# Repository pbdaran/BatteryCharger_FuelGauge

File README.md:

# Breakout Board: Battery Charger & Fuel Gauge — Design Story and Choices

Designing a compact, reliable battery management breakout board isn’t just about cramming chips together — it’s about understanding the trade-offs behind every component choice.  
Here’s the thinking behind the **Battery Charger & Fuel Gauge Breakout Board** and why I chose the ICs I did.

## 1. The Battery Charger: BQ24040 vs. TP4056

The **TP4056** has earned its fame in the maker world — it’s cheap, easy to use, and well supported. But it hides a quirk that can cause headaches in certain designs.

**The TP4056 quirk:**
- Pre-charge threshold: ~3.0 V
- Fixed pre-charge (trickle charge) current: **10 mA**
- If your battery is below 3 V and you have an **LDO** pulling ~10 mA from the charger output (to power 3.3 V logic, for instance), the TP4056 will happily supply that current to the LDO… **and zero to the battery**.
- Result? The battery never rises above 3 V, and the charger never switches to constant current mode. Stalemate.

**How the BQ24040 solves it:**
- **Lower pre-charge threshold**: ~2.5 V (battery starts charging earlier in its discharge)
- **Configurable pre-charge current**: e.g., 50 mA — plenty to both feed your LDO and still trickle energy into the cell.
- Additional perks:
  - Power path management: can supply load and charge battery simultaneously.
  - Status outputs for charge and fault indication.
  - Thermal regulation built in.

This means your system boots faster from a dead battery, and you don’t get stuck in a “never charging” deadlock.

## 2. The Fuel Gauge: BQ27621-G1 and the Calibration Dilemma

Battery fuel gauging is trickier than it looks. You can measure voltage, but it doesn’t tell the whole story about state of charge (SoC).

**Two main approaches:**
1. **Impedance Tracking** — Highly accurate, but requires painful calibration and “training” cycles to match the gauge to your specific cell.  
   Great for high-volume products, less great for quick prototypes or small-run boards.
2. **Voltage Correlation** — Uses cell voltage, temperature, and discharge patterns to estimate SoC. Less accurate over extreme conditions, but easy to set up.

The **BQ27621-G1** uses a **dynamic voltage correlation algorithm**:
- No complex calibration process.
- Good enough accuracy for most portable projects.
- Very low quiescent current — ideal for battery-powered devices.
- I²C interface for easy microcontroller integration.

For a breakout board aimed at prototyping and flexibility, avoiding impedance tracking’s long setup time is worth the small trade-off in accuracy.

## 3. Board Connections and Options

This board isn’t just two chips and some passives — it’s designed to be **flexible** in different setups.

**Key features:**
- **USB input** for charging.
- **Battery JST connector** for Li-Ion/Li-Po cells.
- **Load output** that stays powered even while charging (thanks to the BQ24040’s power path management).
- **I²C interface** (SDA, SCL) for reading fuel gauge data.
- **Configurable pre-charge current** via resistor selection.
- **Charge status pins** for LED indicators or MCU monitoring.

## 4. Why This Combo Works Well

The **BQ24040 + BQ27621-G1** pairing offers:
- Robust charging under low-voltage conditions.
- Accurate-enough battery state reporting without lengthy setup.
- Support for both charging and powering your project at the same time.
- Minimal parts count without sacrificing essential battery management features.

_Refer to the Design Document for the board configurations_

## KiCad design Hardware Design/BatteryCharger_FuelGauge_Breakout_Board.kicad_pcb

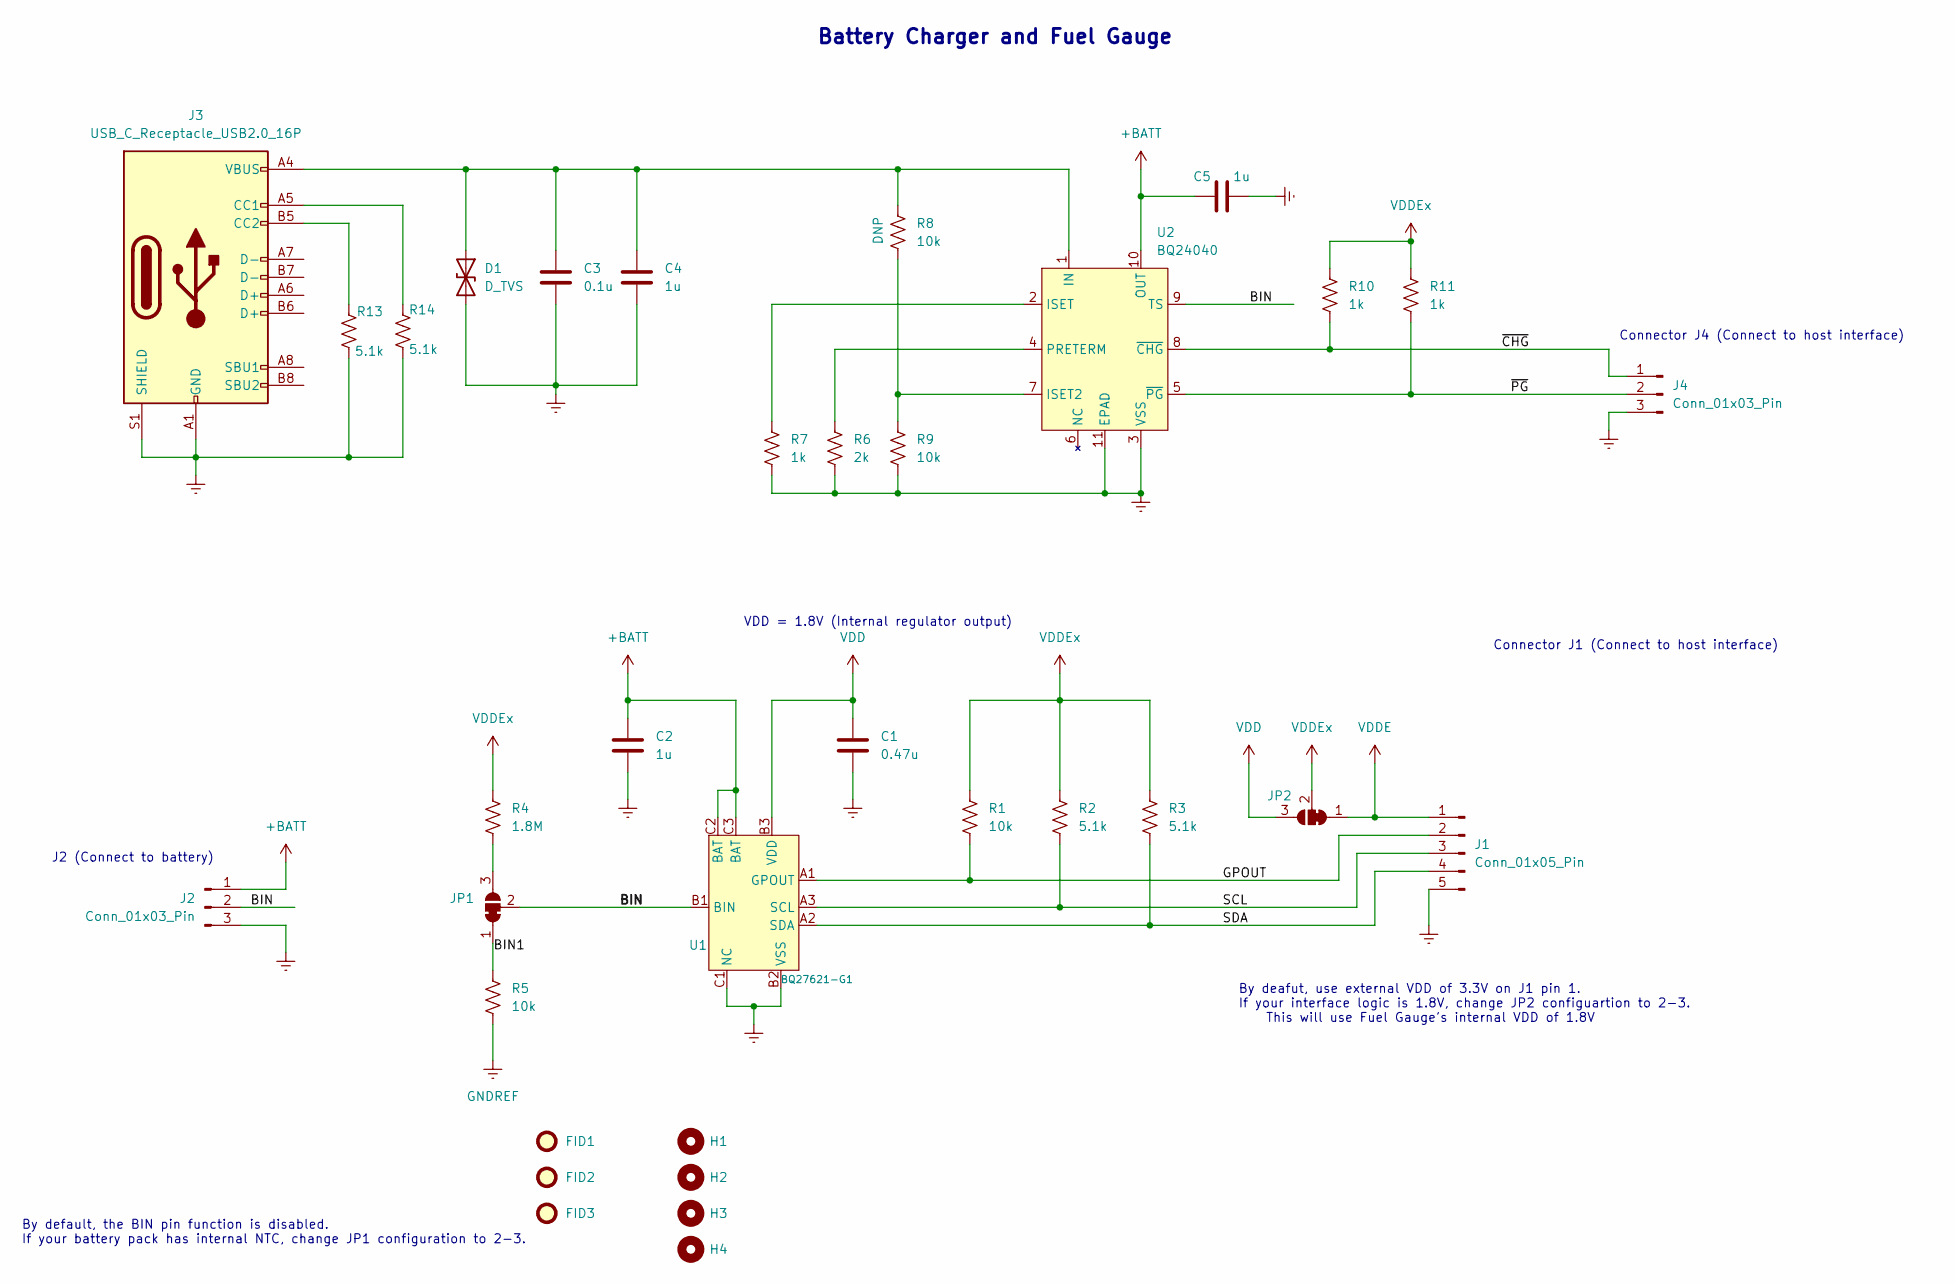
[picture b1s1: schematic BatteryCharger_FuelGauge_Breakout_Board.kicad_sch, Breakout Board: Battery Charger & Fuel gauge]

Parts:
C1: 0.47u; C_0603_1608Metric_Pad1.08x0.95mm_HandSolder; MPN UMK107B7474KA-TR
C2, C4, C5: 1u; C_0603_1608Metric_Pad1.08x0.95mm_HandSolder; MPN CL10B105KO8NNNC
C3: 0.1u; C_0603_1608Metric_Pad1.08x0.95mm_HandSolder; MPN CC0603KRX7R7BB104
D1: D_TVS; D_SMB_Handsoldering; MPN SMBJ7.5CA
FID1, FID2, FID3: Fiducial; Fiducial_0.5mm_Mask1mm
H1, H2, H3, H4: MountingHole; MountingHole_2.2mm_M2
J1: Conn_01x05_Pin; PinHeader_1x05_P2.54mm_Vertical; MPN 61300511121
J2, J4: Conn_01x03_Pin; PinHeader_1x03_P2.54mm_Vertical; MPN G800W305018EU
J3: USB_C_Receptacle_USB2.0_16P; USB_C_Receptacle_GCT_USB4105-xx-A_16P_TopMnt_Horizontal
JP1, JP2: SolderJumper_3_Bridged12; SolderJumper-3_P1.3mm_Bridged12_Pad1.0x1.5mm
R1, R5, R8, R9: 10k; R_0603_1608Metric_Pad0.98x0.95mm_HandSolder; MPN RMCF0603FT10K0
R2, R3: 5.1k; R_0603_1608Metric_Pad0.98x0.95mm_HandSolder; MPN RMCF0603FT5K10
R4: 1.8M; R_0603_1608Metric_Pad0.98x0.95mm_HandSolder; MPN RC0603FR-071M8L
R6: 2k; R_0603_1608Metric_Pad0.98x0.95mm_HandSolder; MPN ERA-3AEB202V
R7, R10, R11: 1k; R_0603_1608Metric_Pad0.98x0.95mm_HandSolder; MPN RMCF0603FT1K00
R13, R14: 5.1k; R_0603_1608Metric_Pad0.98x0.95mm_HandSolder; MPN RC0603FR-075K1L
U1: BQ27621-G1; Texas_DSBGA-9_1.62x1.58mm_Layout3x3_P0.5mm; MPN BQ27621YZFR-G1A
U2: BQ24040; WSON-10-1EP_2x2mm_P0.4mm_EP1.5x0.9mm; MPN BQ24040DSQT

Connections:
+BATT: C2.1, C5.1, J2.1, U1.C2 (BAT), U1.C3 (BAT), U2.10 (OUT)
/BIN: J2.2, JP1.2 (C), U1.B1 (BIN), U2.9 (TS)
/BIN1: JP1.1 (A), R5.1
/GPOUT: J1.2, R1.2, U1.A1 (GPOUT)
/SCL: J1.3, R2.2, U1.A3 (SCL)
/SDA: J1.4, R3.2, U1.A2 (SDA)
/~CHG: J4.1, R10.2, U2.8 (~CHG)
/~PG: J4.2, R11.2, U2.5 (~PG)
GNDREF: C1.2, C2.2, C3.2, C4.2, C5.2, D1.2 (A2), J1.5, J2.3, J3.A1 (GND), J3.A12 (GND), J3.B1 (GND), J3.B12 (GND), J3.S1 (SHIELD), J4.3, R5.2, R6.2, R7.2, R9.2, R13.2, R14.2, U1.B2 (VSS), U1.C1 (NC), U2.3 (VSS), U2.11 (EPAD)
unnamed: C3.1, C4.1, D1.1 (A1), J3.A4 (VBUS), J3.A9 (VBUS), J3.B4 (VBUS), J3.B9 (VBUS), R8.1, U2.1 (IN)
unnamed: J3.A5 (CC1), R14.1
unnamed: J3.B5 (CC2), R13.1
unnamed: JP1.3 (B), R4.2
unnamed: R8.2, R9.1, U2.7 (ISET2)
unnamed: R7.1, U2.2 (ISET)
unnamed: R6.1, U2.4 (PRETERM)
VDD: C1.1, JP2.3 (B), U1.B3 (VDD)
VDDE: J1.1, JP2.1 (A)
VDDEx: JP2.2 (C), R1.1, R2.1, R3.1, R4.1, R10.1, R11.1

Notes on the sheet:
By default, the BIN pin function is disabled. If your battery pack has internal NTC, change JP1 configuration to 2-3.
VDD = 1.8V (Internal regulator output)
Connector J4 (Connect to host interface)
Battery Charger and Fuel Gauge
J2 (Connect to battery)
Connector J1 (Connect to host interface)
By deafut, use external VDD of 3.3V on J1 pin 1. If your interface logic is 1.8V, change JP2 configuartion to 2-3. This will use Fuel Gauge's internal VDD of 1.8V

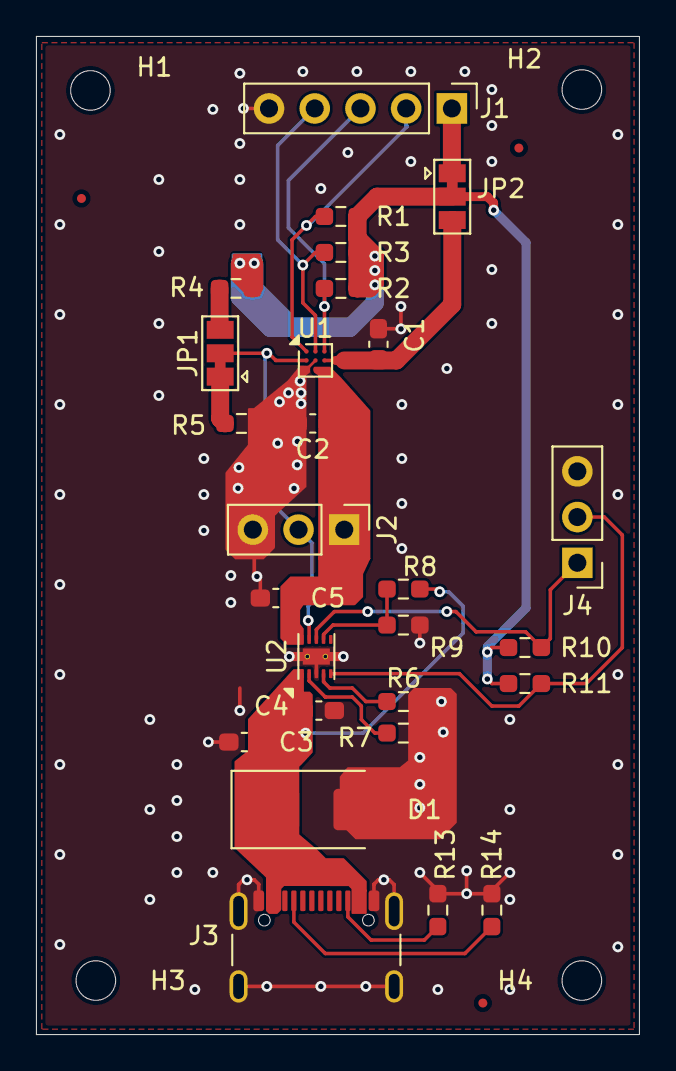
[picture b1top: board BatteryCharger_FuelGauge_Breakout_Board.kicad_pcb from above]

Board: 2 copper layers, 33.5 x 55.5 mm, 34 parts (0 on the bottom side), 19 nets.

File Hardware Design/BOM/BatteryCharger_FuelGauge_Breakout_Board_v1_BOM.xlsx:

S.No. | Reference Designator | Qty | Value | MPN | Manufacturer | Description
1 | U2 | 1 | BQ24040 | BQ24040DSQT | Texas Instruments | IC BATT CHG LI-ION 1CELL 10SON
2 | U1 | 1 | BQ27621-G1 | BQ27621YZFR-G1A | Texas Instruments | IC BATT FUEL GAUGE LIION 9DSBGA
3 | > R7, R10, R11 | 3 | 1k | RMCF0603FT1K00 | Stackpole Electronics Inc | Resistor, US symbol
4 | > R2, R3 | 2 | 5.1k | RMCF0603FT5K10 | Stackpole Electronics Inc | Resistor, US symbol
5 | > R13, R14 | 2 | 5.1k | RC0603FR-075K1L | YAGEO | Resistor, US symbol
6 | > R1, R5, R8, R9 | 4 | 10k | RMCF0603FT10K0 | Stackpole Electronics Inc | Resistor, US symbol
7 | R6 | 1 | 2k | ERA-3AEB202V | Panasonic Electronic Components | Resistor, US symbol
8 | R4 | 1 | 1.8M | RC0603FR-071M8L | YAGEO | Resistor, US symbol
9 | > J2, J4 | 2 | Conn_01x03_Pin | G800W305018EU | Amphenol ICC (Commercial Products) | Generic connector, single row, 01x03, script generated
10 | J1 | 1 | Conn_01x05_Pin | 61300511121 | Würth Elektronik | Generic connector, single row, 01x05, script generated
11 | > FID1-FID3, H1-H4, J3, JP1, JP2 | 10 | -- mixed values -- |  |  | -- mixed values --
12 | D1 | 1 | D_TVS | SMBJ7.5CA | Littlefuse Inc. | Bidirectional transient-voltage-suppression diode
13 | > C2, C4, C5 | 3 | 1u | CL10B105KO8NNNC | Samsung Electro-Mechanics | Unpolarized capacitor
14 | C3 | 1 | 0.1u | CC0603KRX7R7BB104 | YAGEO | Unpolarized capacitor
15 | C1 | 1 | 0.47u | UMK107B7474KA-TR | Taiyo Yuden | Unpolarized capacitor
